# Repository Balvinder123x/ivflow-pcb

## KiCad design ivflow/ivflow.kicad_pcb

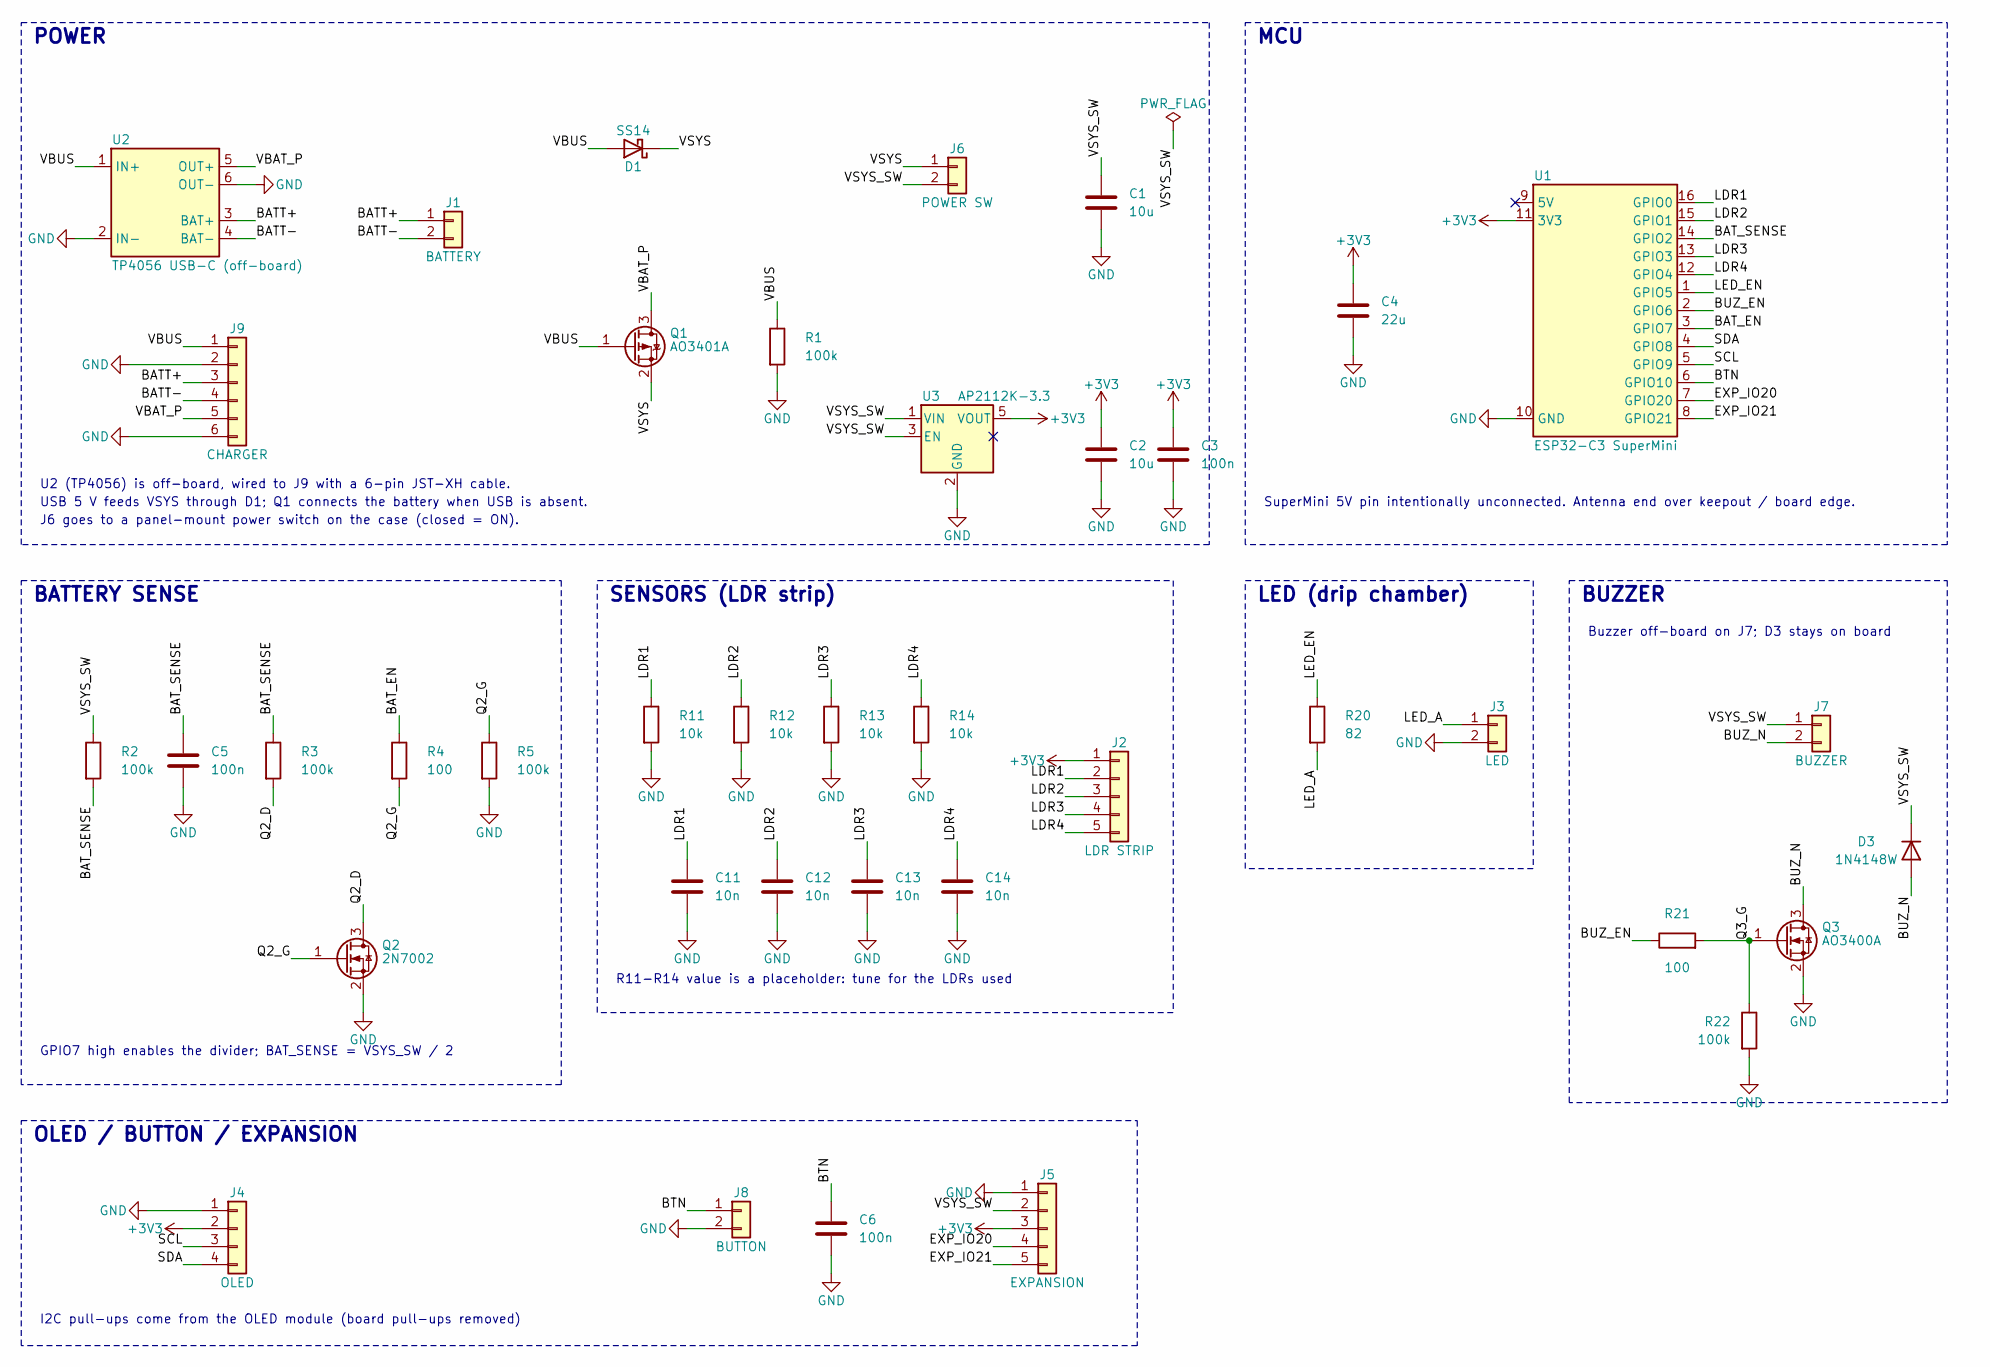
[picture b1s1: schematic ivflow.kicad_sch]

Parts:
C1, C2: 10u; C_0805_2012Metric_Pad1.18x1.45mm_HandSolder; LCSC C15850
C3, C5, C6: 100n; C_0805_2012Metric_Pad1.18x1.45mm_HandSolder; LCSC C49678
C4: 22u; C_0805_2012Metric_Pad1.18x1.45mm_HandSolder; LCSC C45783
C11, C12, C13, C14: 10n; C_0805_2012Metric_Pad1.18x1.45mm_HandSolder; LCSC C1710
D1: SS14; D_SMA_Handsoldering; LCSC C2480
D3: 1N4148W; D_SOD-123; LCSC C81598
J1: BATTERY; JST_PH_B2B-PH-K_1x02_P2.00mm_Vertical; LCSC C131337
J2: LDR STRIP; JST_XH_B5B-XH-A_1x05_P2.50mm_Vertical; LCSC C157991
J3: LED; JST_XH_B2B-XH-A_1x02_P2.50mm_Vertical; LCSC C158012
J4: OLED; PinHeader_1x04_P2.54mm_Vertical
J5: EXPANSION; PinHeader_1x05_P2.54mm_Vertical
J6: POWER SW; JST_XH_B2B-XH-A_1x02_P2.50mm_Vertical; LCSC C158012
J7: BUZZER; JST_XH_B2B-XH-A_1x02_P2.50mm_Vertical; LCSC C158012
J8: BUTTON; JST_XH_B2B-XH-A_1x02_P2.50mm_Vertical; LCSC C158012
J9: CHARGER; JST_XH_B6B-XH-A_1x06_P2.50mm_Vertical; LCSC C144397
Q1: AO3401A; SOT-23_Handsoldering; LCSC C15127
Q2: 2N7002; SOT-23_Handsoldering; LCSC C8545
Q3: AO3400A; SOT-23_Handsoldering; LCSC C20917
R1, R2, R3, R5, R22: 100k; R_0805_2012Metric_Pad1.20x1.40mm_HandSolder; LCSC C149504
R4, R21: 100; R_0805_2012Metric_Pad1.20x1.40mm_HandSolder; LCSC C17408
R11, R12, R13, R14: 10k; R_0805_2012Metric_Pad1.20x1.40mm_HandSolder; LCSC C17414
R20: 82; R_0805_2012Metric_Pad1.20x1.40mm_HandSolder; LCSC C17841
U1: ESP32-C3 SuperMini; ESP32-C3_SuperMini
U2: TP4056 USB-C (off-board)
U3: AP2112K-3.3; SOT-23-5_HandSoldering; LCSC C51118

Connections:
+3V3: C2.1, C3.1, C4.1, J2.1, J4.2, J5.3, U1.11 (3V3), U3.5 (VOUT)
/BATT+: J1.1, J9.3, U2.3 (BAT+)
/BATT-: J1.2, J9.4, U2.4 (BAT-)
/BAT_EN: R4.1, U1.3 (GPIO7)
/BAT_SENSE: C5.1, R2.2, R3.1, U1.14 (GPIO2)
/BTN: C6.1, J8.1, U1.6 (GPIO10)
/BUZ_EN: R21.1, U1.2 (GPIO6)
/BUZ_N: D3.2 (A), J7.2, Q3.3 (D)
/EXP_IO20: J5.4, U1.7 (GPIO20)
/EXP_IO21: J5.5, U1.8 (GPIO21)
/LDR1: C11.1, J2.2, R11.1, U1.16 (GPIO0)
/LDR2: C12.1, J2.3, R12.1, U1.15 (GPIO1)
/LDR3: C13.1, J2.4, R13.1, U1.13 (GPIO3)
/LDR4: C14.1, J2.5, R14.1, U1.12 (GPIO4)
/LED_A: J3.1, R20.2
/LED_EN: R20.1, U1.1 (GPIO5)
/Q2_D: Q2.3 (D), R3.2
/Q2_G: Q2.1 (G), R4.2, R5.1
/Q3_G: Q3.1 (G), R21.2, R22.1
/SCL: J4.3, U1.5 (GPIO9)
/SDA: J4.4, U1.4 (GPIO8)
/VBAT_P: J9.5, Q1.3 (D), U2.5 (OUT+)
/VBUS: D1.2 (A), J9.1, Q1.1 (G), R1.1, U2.1 (IN+)
/VSYS: D1.1 (K), J6.1, Q1.2 (S)
/VSYS_SW: C1.1, D3.1 (K), J5.2, J6.2, J7.1, R2.1, U3.1 (VIN), U3.3 (EN)
GND: C1.2, C2.2, C3.2, C4.2, C5.2, C6.2, C11.2, C12.2, C13.2, C14.2, J3.2, J4.1, J5.1, J8.2, J9.2, J9.6, Q2.2 (S), Q3.2 (S), R1.2, R5.2, R11.2, R12.2, R13.2, R14.2, R22.2, U1.10 (GND), U2.2 (IN-), U2.6 (OUT-), U3.2 (GND)

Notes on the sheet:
POWER
MCU
BATTERY SENSE
SENSORS (LDR strip)
LED (drip chamber)
BUZZER
OLED / BUTTON / EXPANSION
USB 5 V feeds VSYS through D1; Q1 connects the battery when USB is absent.
J6 goes to a panel-mount power switch on the case (closed = ON).
U2 (TP4056) is off-board, wired to J9 with a 6-pin JST-XH cable.
SuperMini 5V pin intentionally unconnected. Antenna end over keepout / board edge.
Buzzer off-board on J7; D3 stays on board
GPIO7 high enables the divider; BAT_SENSE = VSYS_SW / 2
R11-R14 value is a placeholder: tune for the LDRs used
I2C pull-ups come from the OLED module (board pull-ups removed)

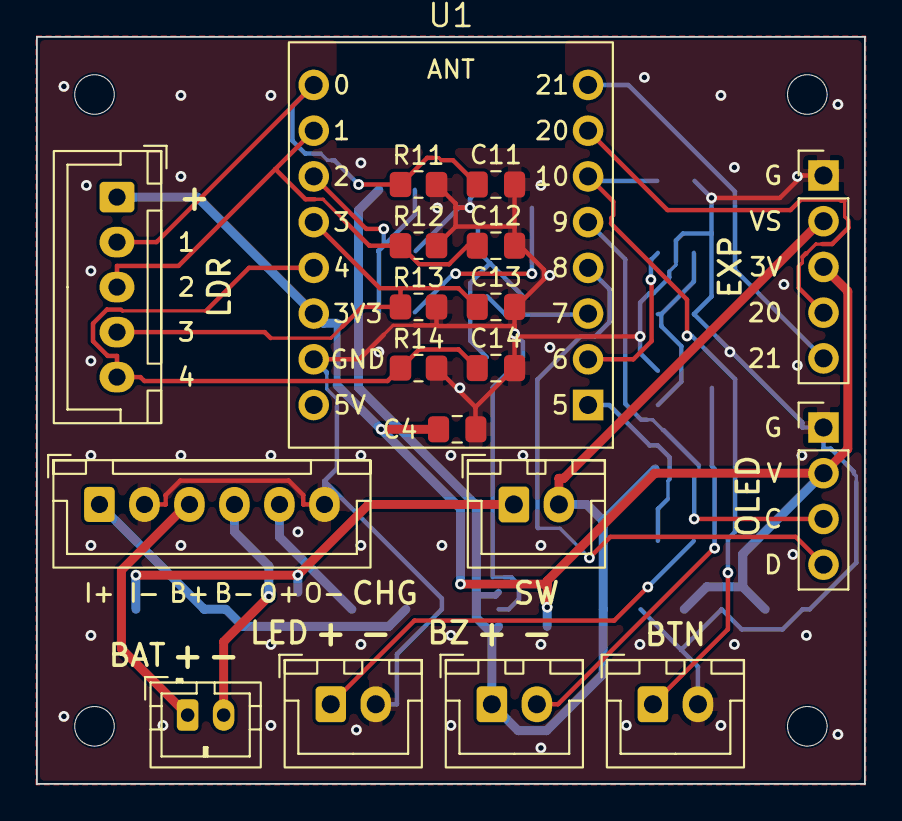
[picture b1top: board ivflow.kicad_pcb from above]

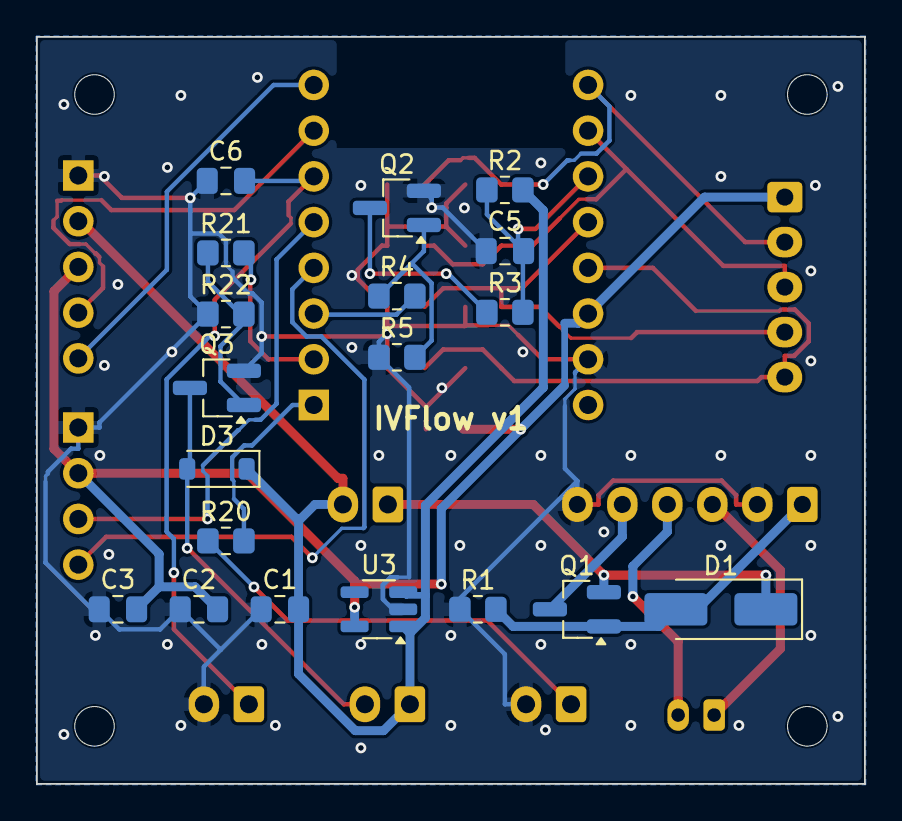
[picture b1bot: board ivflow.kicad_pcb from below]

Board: 2 copper layers, 46.0 x 41.5 mm, 42 parts (19 on the bottom side), 26 nets.

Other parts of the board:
H1, H2, H3, H4: MountingHole_2.2mm_M2

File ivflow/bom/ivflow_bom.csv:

"Designator","Value","Footprint","LCSC","Qty","DNP"
"C1,C2","10u","Capacitor_SMD:C_0805_2012Metric_Pad1.18x1.45mm_HandSolder","C15850","2",""
"C3,C5,C6","100n","Capacitor_SMD:C_0805_2012Metric_Pad1.18x1.45mm_HandSolder","C49678","3",""
"C4","22u","Capacitor_SMD:C_0805_2012Metric_Pad1.18x1.45mm_HandSolder","C45783","1",""
"C11,C12,C13,C14","10n","Capacitor_SMD:C_0805_2012Metric_Pad1.18x1.45mm_HandSolder","C1710","4",""
"D1","SS14","Diode_SMD:D_SMA_Handsoldering","C2480","1",""
"D3","1N4148W","Diode_SMD:D_SOD-123","C81598","1",""
"J1","BATTERY","Connector_JST:JST_PH_B2B-PH-K_1x02_P2.00mm_Vertical","C131337","1",""
"J2","LDR STRIP","Connector_JST:JST_XH_B5B-XH-A_1x05_P2.50mm_Vertical","C157991","1",""
"J3","LED","Connector_JST:JST_XH_B2B-XH-A_1x02_P2.50mm_Vertical","C158012","1",""
"J4","OLED","Connector_PinHeader_2.54mm:PinHeader_1x04_P2.54mm_Vertical","","1",""
"J5","EXPANSION","Connector_PinHeader_2.54mm:PinHeader_1x05_P2.54mm_Vertical","","1",""
"J6","POWER SW","Connector_JST:JST_XH_B2B-XH-A_1x02_P2.50mm_Vertical","C158012","1",""
"J7","BUZZER","Connector_JST:JST_XH_B2B-XH-A_1x02_P2.50mm_Vertical","C158012","1",""
"J8","BUTTON","Connector_JST:JST_XH_B2B-XH-A_1x02_P2.50mm_Vertical","C158012","1",""
"J9","CHARGER","Connector_JST:JST_XH_B6B-XH-A_1x06_P2.50mm_Vertical","C144397","1",""
"Q1","AO3401A","Package_TO_SOT_SMD:SOT-23_Handsoldering","C15127","1",""
"Q2","2N7002","Package_TO_SOT_SMD:SOT-23_Handsoldering","C8545","1",""
"Q3","AO3400A","Package_TO_SOT_SMD:SOT-23_Handsoldering","C20917","1",""
"R1,R2,R3,R5,R22","100k","Resistor_SMD:R_0805_2012Metric_Pad1.20x1.40mm_HandSolder","C149504","5",""
"R4,R21","100","Resistor_SMD:R_0805_2012Metric_Pad1.20x1.40mm_HandSolder","C17408","2",""
"R11,R12,R13,R14","10k","Resistor_SMD:R_0805_2012Metric_Pad1.20x1.40mm_HandSolder","C17414","4",""
"R20","82","Resistor_SMD:R_0805_2012Metric_Pad1.20x1.40mm_HandSolder","C17841","1",""
"U1","ESP32-C3 SuperMini","ivflow_lib:ESP32-C3_SuperMini","","1",""
"U2","TP4056 USB-C (off-board)","","","1",""
"U3","AP2112K-3.3","Package_TO_SOT_SMD:SOT-23-5_HandSoldering","C51118","1",""

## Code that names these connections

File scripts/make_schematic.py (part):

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    # ---- MCU
    dict(ref="U1", lib="ivflow_lib:ESP32-C3_SuperMini", value="ESP32-C3 SuperMini", block="MCU", at=(20, 16),
         nets={"5V": NC, "3V3": "+3V3", "GND": "GND",
               "GPIO0": "LDR1", "GPIO1": "LDR2", "GPIO2": "BAT_SENSE", "GPIO3": "LDR3", "GPIO4": "LDR4",
               "GPIO5": "LED_EN", "GPIO6": "BUZ_EN", "GPIO7": "BAT_EN", "GPIO8": "SDA", "GPIO9": "SCL",
               "GPIO10": "BTN", "GPIO20": "EXP_IO20", "GPIO21": "EXP_IO21"},
         fp="ivflow_lib:ESP32-C3_SuperMini"),
    dict(ref="C4", lib="Device:C", value="22u", block="MCU", at=(6, 16), nets={"1": "+3V3", "2": "GND"},
         desc="Bulk capacitor, place next to U1 3V3 pin"),
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    dict(ref="R20", lib="Device:R", value="82", block="LED (drip chamber)", at=(4, 8),
         nets={"1": "LED_EN", "2": "LED_A"}),
    dict(ref="J3", lib="Connector_Generic:Conn_01x02", value="LED", block="LED (drip chamber)", at=(14, 8),
         nets={"1": "LED_A", "2": "GND"}, desc="JST-XH 2-pin to the off-board 5 mm LED. 1 = anode (+)",
         fp=FP_XH2, lcsc=LCSC_XH2),
    # ---- BUZZER
    dict(ref="J7", lib="Connector_Generic:Conn_01x02", value="BUZZER", block="BUZZER", at=(14, 8),
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         desc="1x4 2.54 mm header, jumper wires to the I2C OLED", fp=FP_HDR.format(4)),
    dict(ref="J8", lib="Connector_Generic:Conn_01x02", value="BUTTON", block="OLED / BUTTON / EXPANSION",
         at=(40, 5), nets={"1": "BTN", "2": "GND"}, fp=FP_XH2, lcsc=LCSC_XH2,
         desc="JST-XH 2-pin to the off-board push button (BTN to GND)"),
    dict(ref="C6", lib="Device:C", value="100n", block="OLED / BUTTON / EXPANSION", at=(45, 6),
         nets={"1": "BTN", "2": "GND"}),
    dict(ref="J5", lib="Connector_Generic:Conn_01x05", value="EXPANSION", block="OLED / BUTTON / EXPANSION",
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    ("POWER", (1, 26), "U2 (TP4056) is off-board, wired to J9 with a 6-pin JST-XH cable."),
    ("MCU", (1, 27), "SuperMini 5V pin intentionally unconnected. Antenna end over keepout / board edge."),
    ("BUZZER", (1, 3.2), "Buzzer off-board on J7; D3 stays on board"),
    ("BATTERY SENSE", (1, 26.5), "GPIO7 high enables the divider; BAT_SENSE = VSYS_SW / 2"),
    ("SENSORS (LDR strip)", (1, 22.5), "R11-R14 value is a placeholder: tune for the LDRs used"),
    ("OLED / BUTTON / EXPANSION", (1, 11.4), "I2C pull-ups come from the OLED module (board pull-ups removed)"),
]
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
